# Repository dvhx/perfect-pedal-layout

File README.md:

# perfect-pedal-layout
Perfect single-board guitar pedal layout for 1590N1 (125B) enclosure

# Goals

- all on one board
- no off-board wiring, ribbon cables, or board connectors
- top mounted jacks and standard DC barrel jack
- easy insertion into enclosure
- works both with through hole and SMD components
- only standard and available parts
- no oval holes in enclosure

# Results

Directory "kicad" contains Kicad project with the PCB including 3D models.
You can also install included footprints and symbols library.
This is how it looks like:

# Components

- 6.35mm stereo jack [PJ-609BA](https://lcsc.com/product-detail/Audio-Connectors_HOOYA-PJ-609BA_C309277.html)
  Note: you can only use these style of jacks where metal nut is inserted from the outside, if you use other variant where 
  nut goes over the barrel, like [this one](https://lcsc.com/product-detail/image/PJ-609_C309274.html) you will have trouble 
  inserting PCB into enclosure! With PJ-609BA the PCB goes straight into enclosiure, not rotating, moving in two directions, 
  just straight up.

- Standard DC barrel jack [DC-005 2.0](https://lcsc.com/product-detail/DC-Power-Connectors_BOOMELE-Boom-Precision-Elec-DC-005-2-0_C16214.html)

- Standard 3PDT stomp switch, just search "3PDT pedal switch" on aliexpress

- Optional polarity protection diodes, optional LED indicator diodes, resistors, caps.

- Optional internal battery connector via 2pin JST-XH connector.

# Notes

- Pots used in the demo above are AlpsAlpine RK097 on a perfboard daugterboards
- RK097 (in mono variant) are notable in that they can fit above the jacks thus leaving even more space in the middle, but they would not fit above jacks in 1590B enclosure!
- When using perfboard variant you can symmetrically place 2,3 or 4 RK097 pots in a row
- You can also use "Alpha pots" (WH148) but then only will 3 fit in a row
- You can also use long-shaft pots or long leg pots but they are bit harder to find and you will have less space for the components
- 125B is chinese name for knockoff 1590N1
- In 1590N1 the corners of jacks stick out 0.3mm which is fine, but in 1590B the stickout would be 2.3mm which is too much (you would have to use non-standard 2mm DC jack)
- If you don't see 3D models install provided footprint library and call it "perfect-pedal-layout-footprints"

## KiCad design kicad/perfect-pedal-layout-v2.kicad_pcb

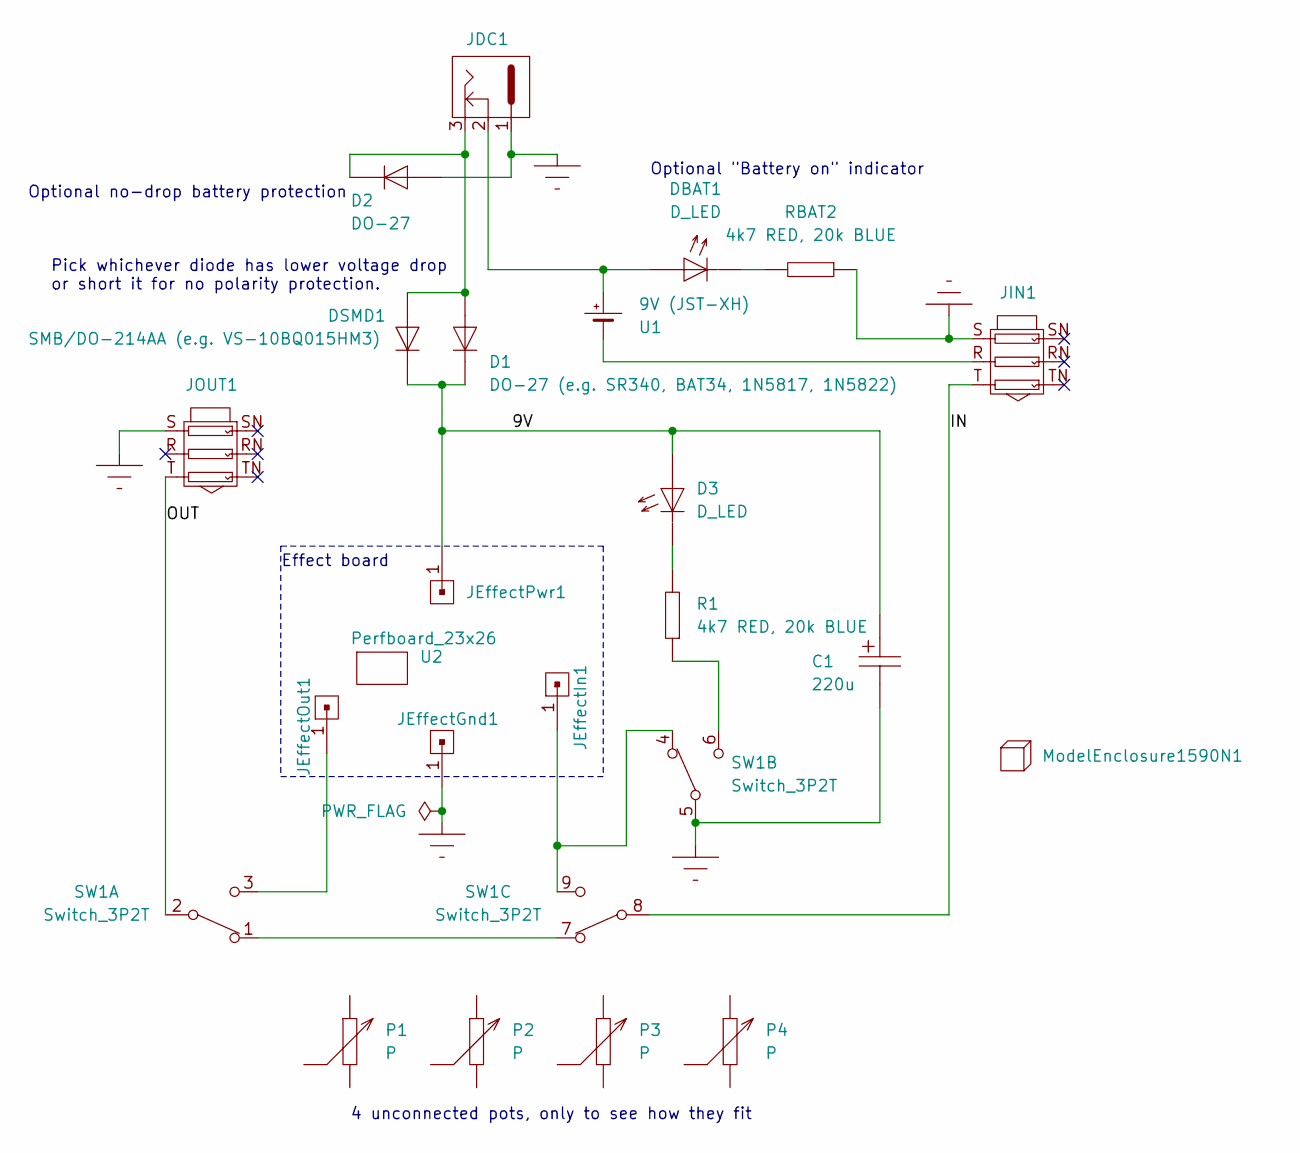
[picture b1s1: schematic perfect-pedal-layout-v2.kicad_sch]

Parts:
C1: 220u; C_polarized_D6.35mm_H5.65mm_P2.54mm
D1: DO-27 (e.g. SR340, BAT34, 1N5817, 1N5822); D_DO-27
D2: DO-27; D_DO-27
D3: D_LED; D_LED_3mm
DBAT1: D_LED; D_LED_3mm
DSMD1: SMB/DO-214AA (e.g. VS-10BQ015HM3); D_SMB
JDC1: Connector_DC_jack_3pin; Connector_DC_005_2.0
JEffectGnd1: Header_1x1_male; Header_1x1_male_upright
JEffectIn1: Header_1x1_male; Header_1x1_male_upright
JEffectOut1: Header_1x1_male; Header_1x1_male_upright
JEffectPwr1: Header_1x1_male; Header_1x1_male_upright
JIN1: Connector_Jack_6.35mm_female_stereo
JOUT1: Connector_Jack_6.35mm_female_stereo
ModelEnclosure1590N1: Model; Enclosure_1590N1
P1, P2, P3, P4: P; P_Daugterboard_Mono_NC
R1: 4k7 RED, 20k BLUE; R_0.25W
RBAT2: 4k7 RED, 20k BLUE; R_0.25W_vertical
SW1: Switch_3P2T; Switch_3PDT
U1: 9V (JST-XH); Battery_JST_XH_female_2pin
U2: Perfboard_23x26

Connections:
/9V: C1.P, D1.K, D3.A, DSMD1.K, JEffectPwr1.1
/IN: JIN1.T, SW1.8
/OUT: JOUT1.T, SW1.2; also elsewhere on the board
GND: C1.N, D2.A, JDC1.1, JEffectGnd1.1, JIN1.S, JOUT1.S, RBAT2.1, SW1.5; also elsewhere on the board
unnamed: D1.A, D2.K, DSMD1.A, JDC1.3
unnamed: D3.K, R1.2
unnamed: DBAT1.A, JDC1.2, U1.P
unnamed: DBAT1.K, RBAT2.2
unnamed: JEffectIn1.1, SW1.4, SW1.9
unnamed: JEffectOut1.1, SW1.3
unnamed: JIN1.R, U1.N
unnamed: R1.1, SW1.6
unnamed: SW1.1, SW1.7

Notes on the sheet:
Optional no-drop battery protection
Effect board
4 unconnected pots, only to see how they fit
Pick whichever diode has lower voltage drop or short it for no polarity protection.
Optional "Battery on" indicator

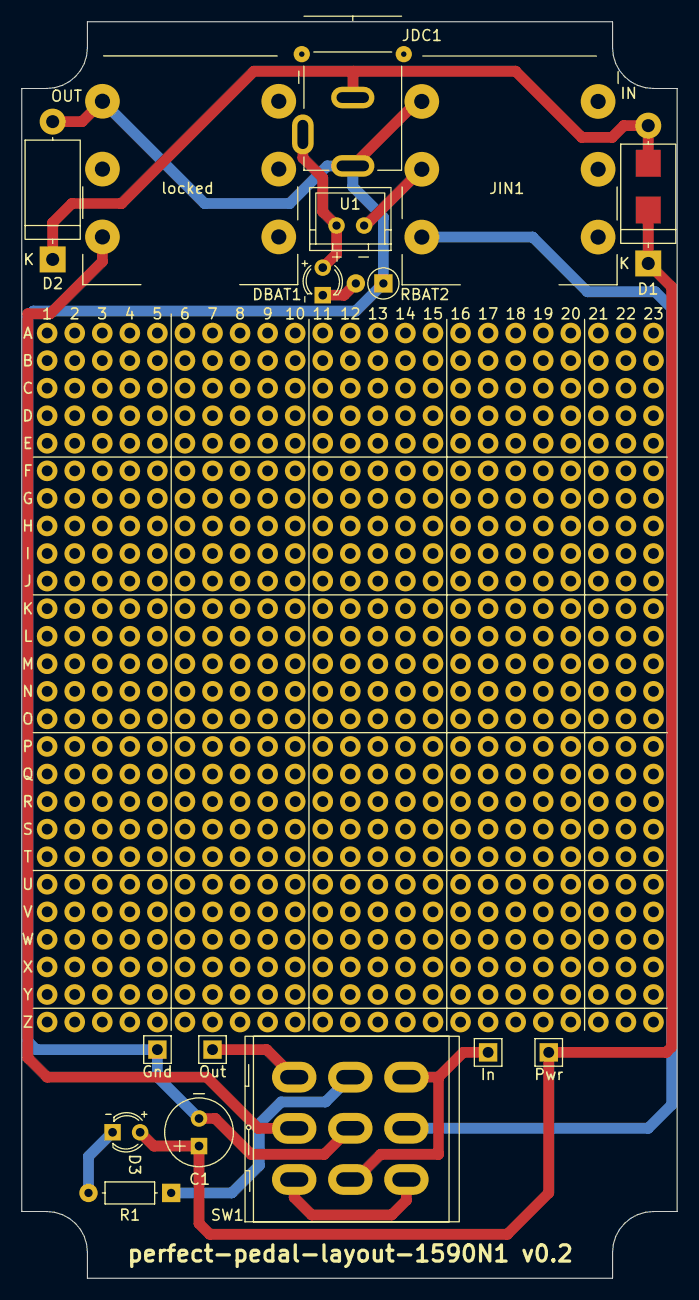
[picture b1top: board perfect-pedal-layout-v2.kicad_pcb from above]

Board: 2 copper layers, 60.4 x 115.8 mm, 23 parts (0 on the bottom side), 13 nets.

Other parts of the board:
locked: Connector_Jack_6.35mm_female_stereo

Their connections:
/OUT: locked.T; also elsewhere on the board
GND: locked.S; also elsewhere on the board

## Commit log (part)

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2025-07-09 Added side view
2025-07-09 Note on 3d models
